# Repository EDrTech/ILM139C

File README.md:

&nbsp;
###### <sub>Quick access</sub>
---------------------------------------------------------------------------------

<p align="center">

</p>

---------------------------------------------------------------------------------
&nbsp;
&nbsp;
&nbsp;
---------------------------------------------------------------------------------
> [!WARNING]
> <p>
> This project is currently under active development. It is experimental, and may not function as intended. The source files might not exactly match tested hardware if you can see this message. Use at your own risk.
><br clear="right"/>
></p>

---------------------------------------------------------------------------------
# Illumicro ILM139C 13x9 RGB LED matrix

ILM139C Is an RGB LED module with a matrix of 13x9 RGB LEDs.
It is based on the IS31FL3741A LED matrix driver, which provides an i2c interface for full control of
individual LEDs which is accessible with a standard QWIIC connector. 
QWIIC Connector allows for up to 4 modules to be connected together on a single i2c bus.
Small form factor of 26mm*18mm and 2mm pitch of LEDs allows for creating small 
high density and high brightness displays.

https://github.com/user-attachments/assets/0ada246c-68c4-4b34-9f10-4a2aee3bf7c3

&nbsp;
&nbsp;
&nbsp;
&nbsp;
&nbsp;
&nbsp;
&nbsp;
&nbsp;
&nbsp;
&nbsp;

# Features
&nbsp;
&nbsp;
&nbsp;
&nbsp;
&nbsp;
<p>

- Very small footprint of 26mm*18mm
- 13x9 RBG LED matrix
- 1mm*1mm LEDs, with 2mm pitch
- IS31FL3741A Driver
- 2.7V~5.5V Operating voltage
- QWIIC Connector
- Selectable i2c address
- Removable driver/matrix boards
- Separate power supply connector
  
</p>
&nbsp;
&nbsp;
&nbsp;

# ILM139C Module pinout

---------------------------------------------------------------------------------

# Installation and set up

Connect QWIIC cable to one of the available connectors on the bottom of the module. If you want to power the module over QWIIC, the jumper resistor should be soldered on the bottom of the module. If the jumper is present, DO NOT connect external power supply as it will short to 3.3V of the QWIIC!
The module can be programmed over i2c, a library is currently under development to allow straightforward integration with and i2c capable device.

&nbsp;
&nbsp;
&nbsp;

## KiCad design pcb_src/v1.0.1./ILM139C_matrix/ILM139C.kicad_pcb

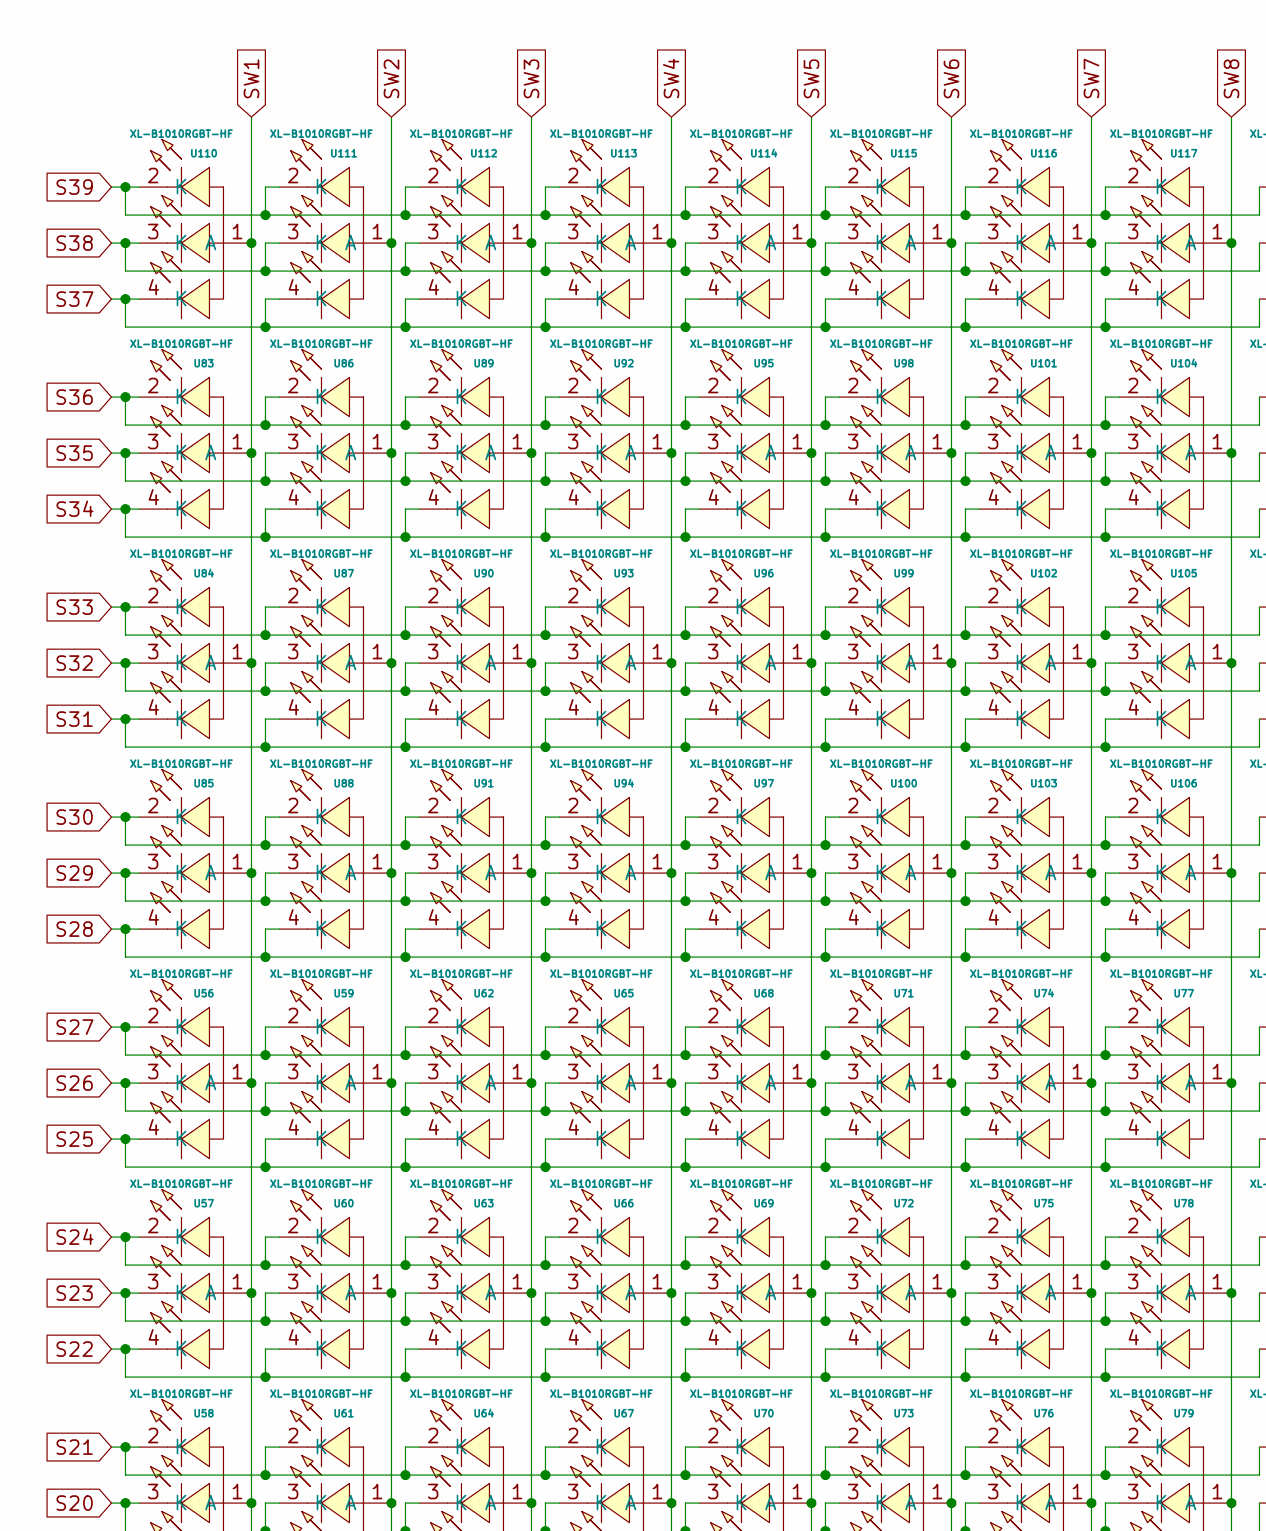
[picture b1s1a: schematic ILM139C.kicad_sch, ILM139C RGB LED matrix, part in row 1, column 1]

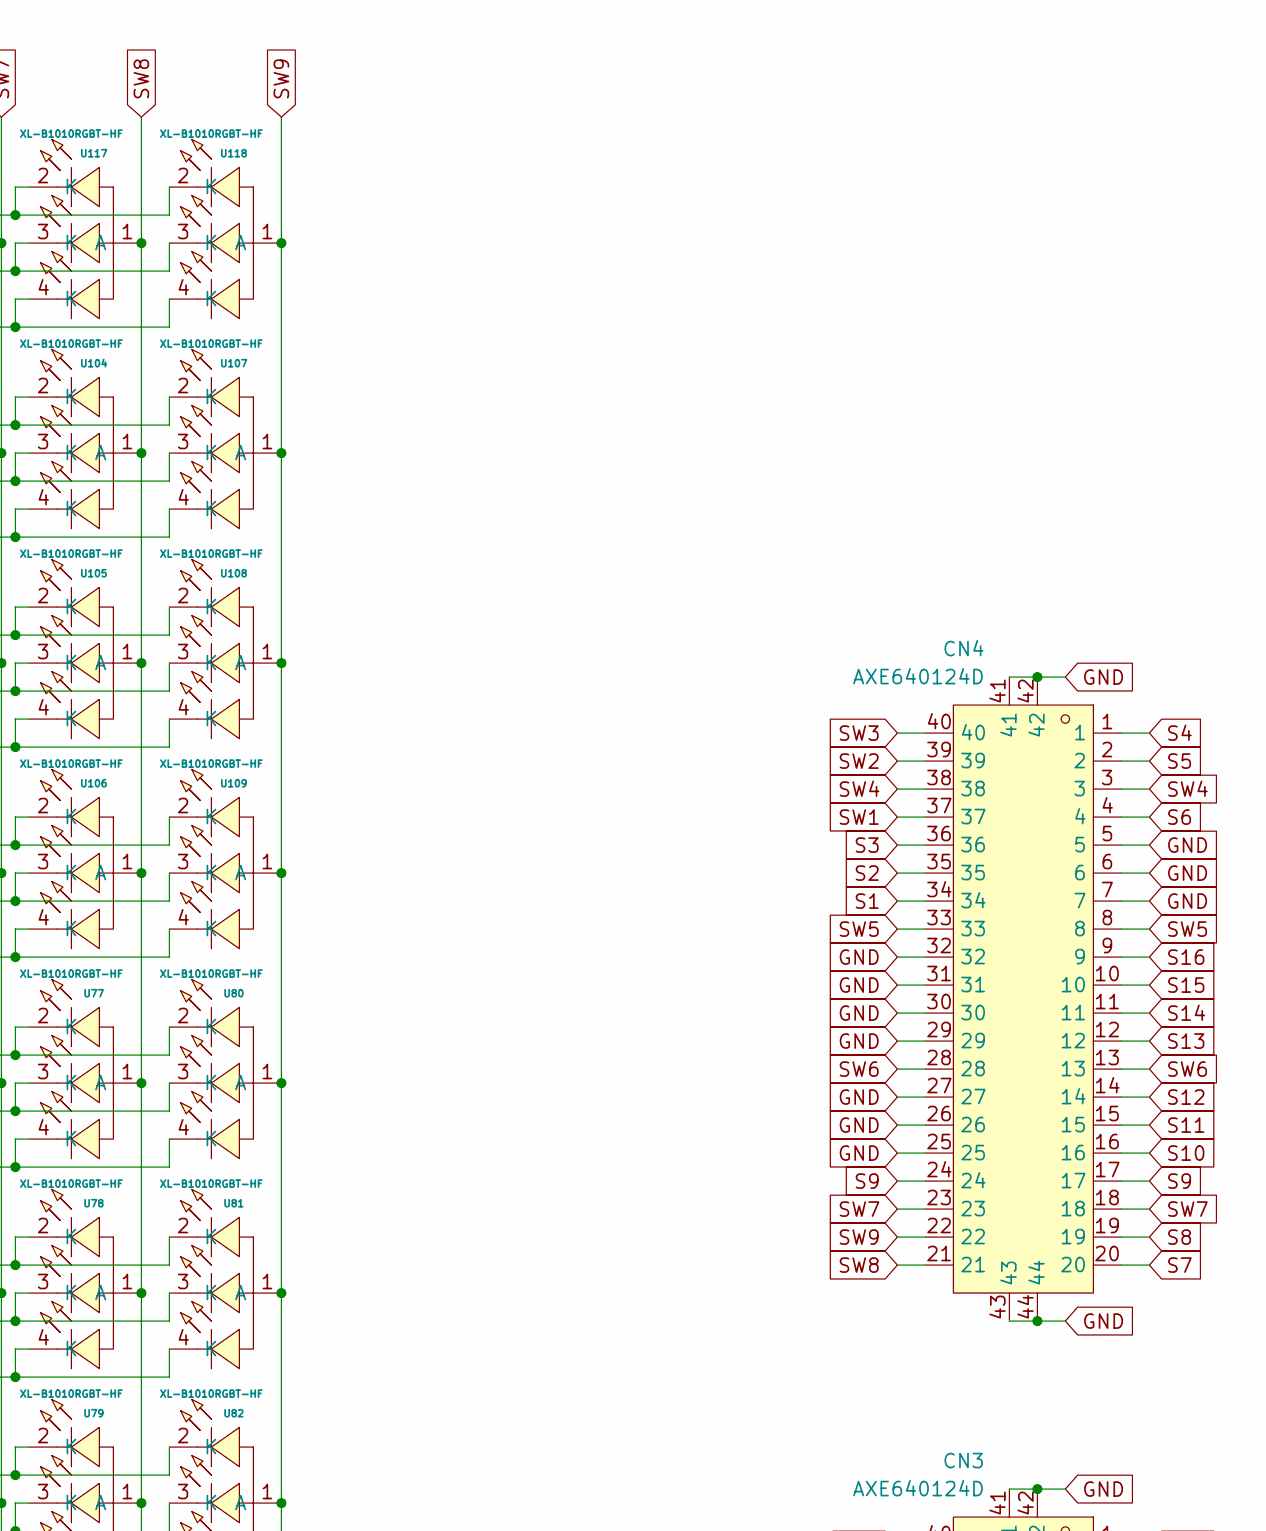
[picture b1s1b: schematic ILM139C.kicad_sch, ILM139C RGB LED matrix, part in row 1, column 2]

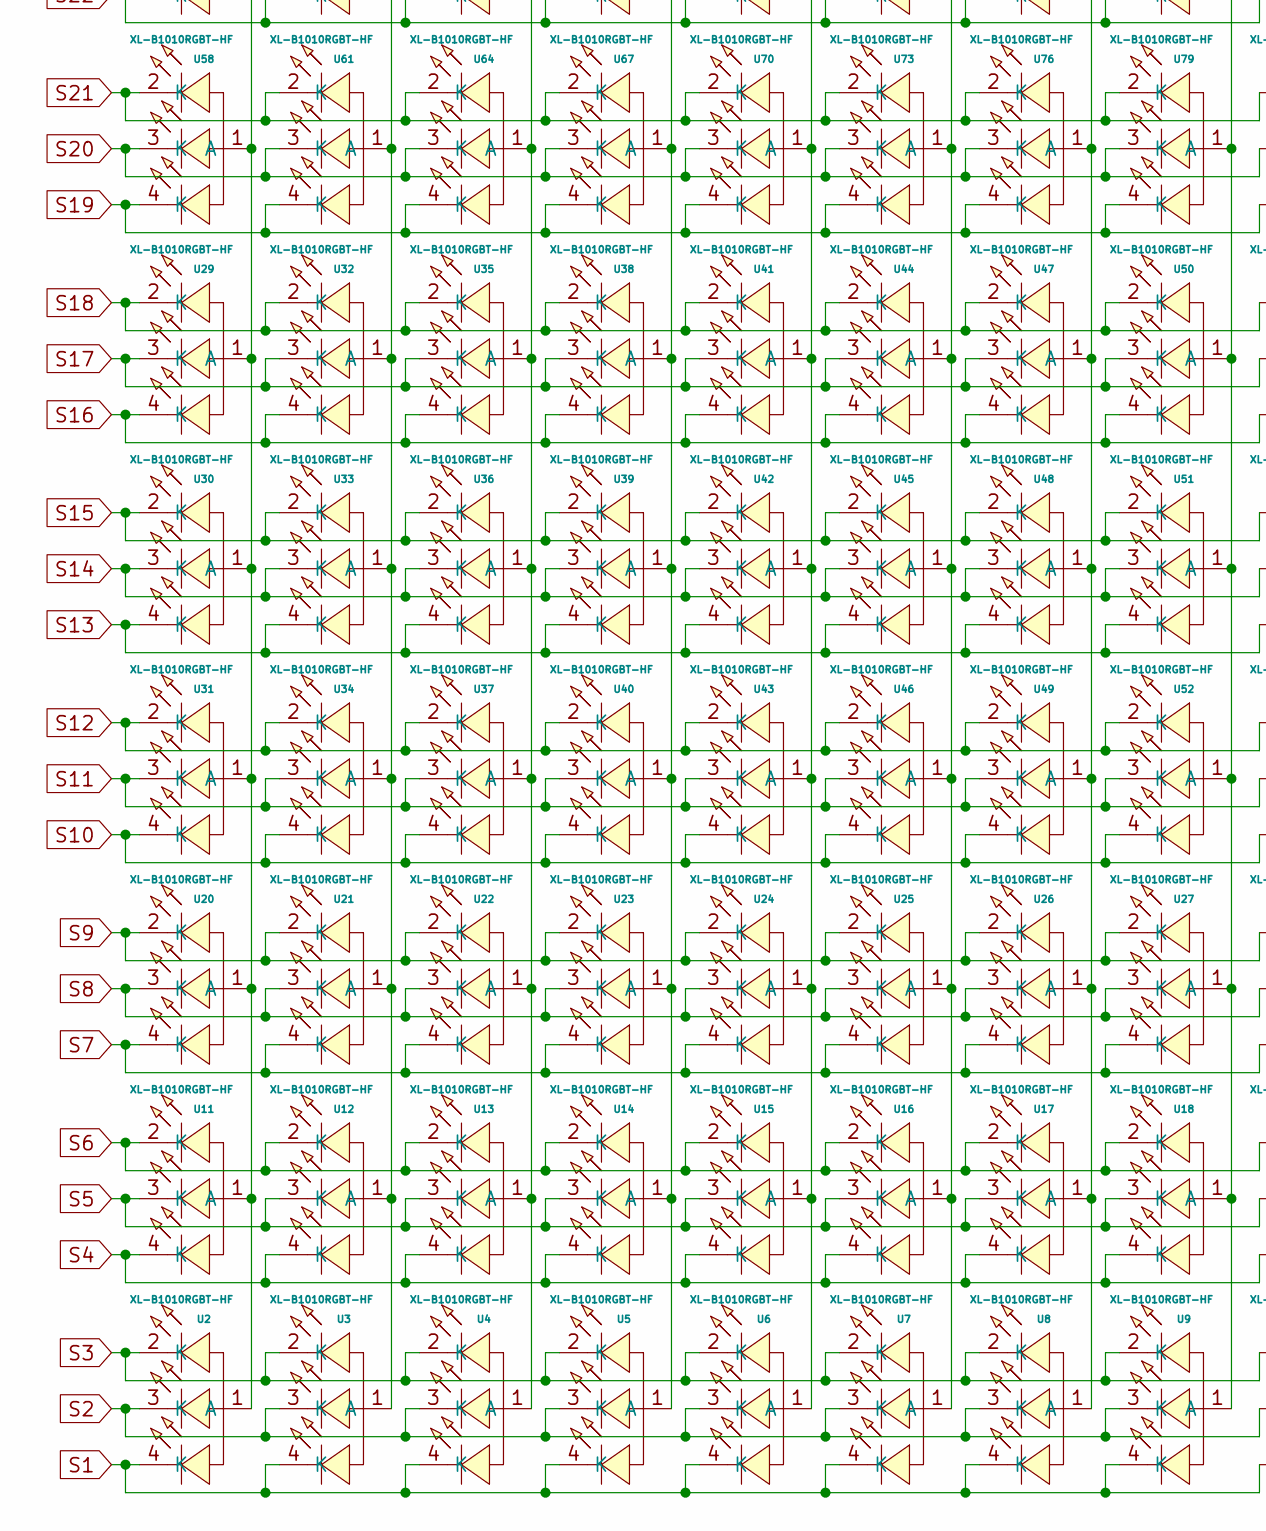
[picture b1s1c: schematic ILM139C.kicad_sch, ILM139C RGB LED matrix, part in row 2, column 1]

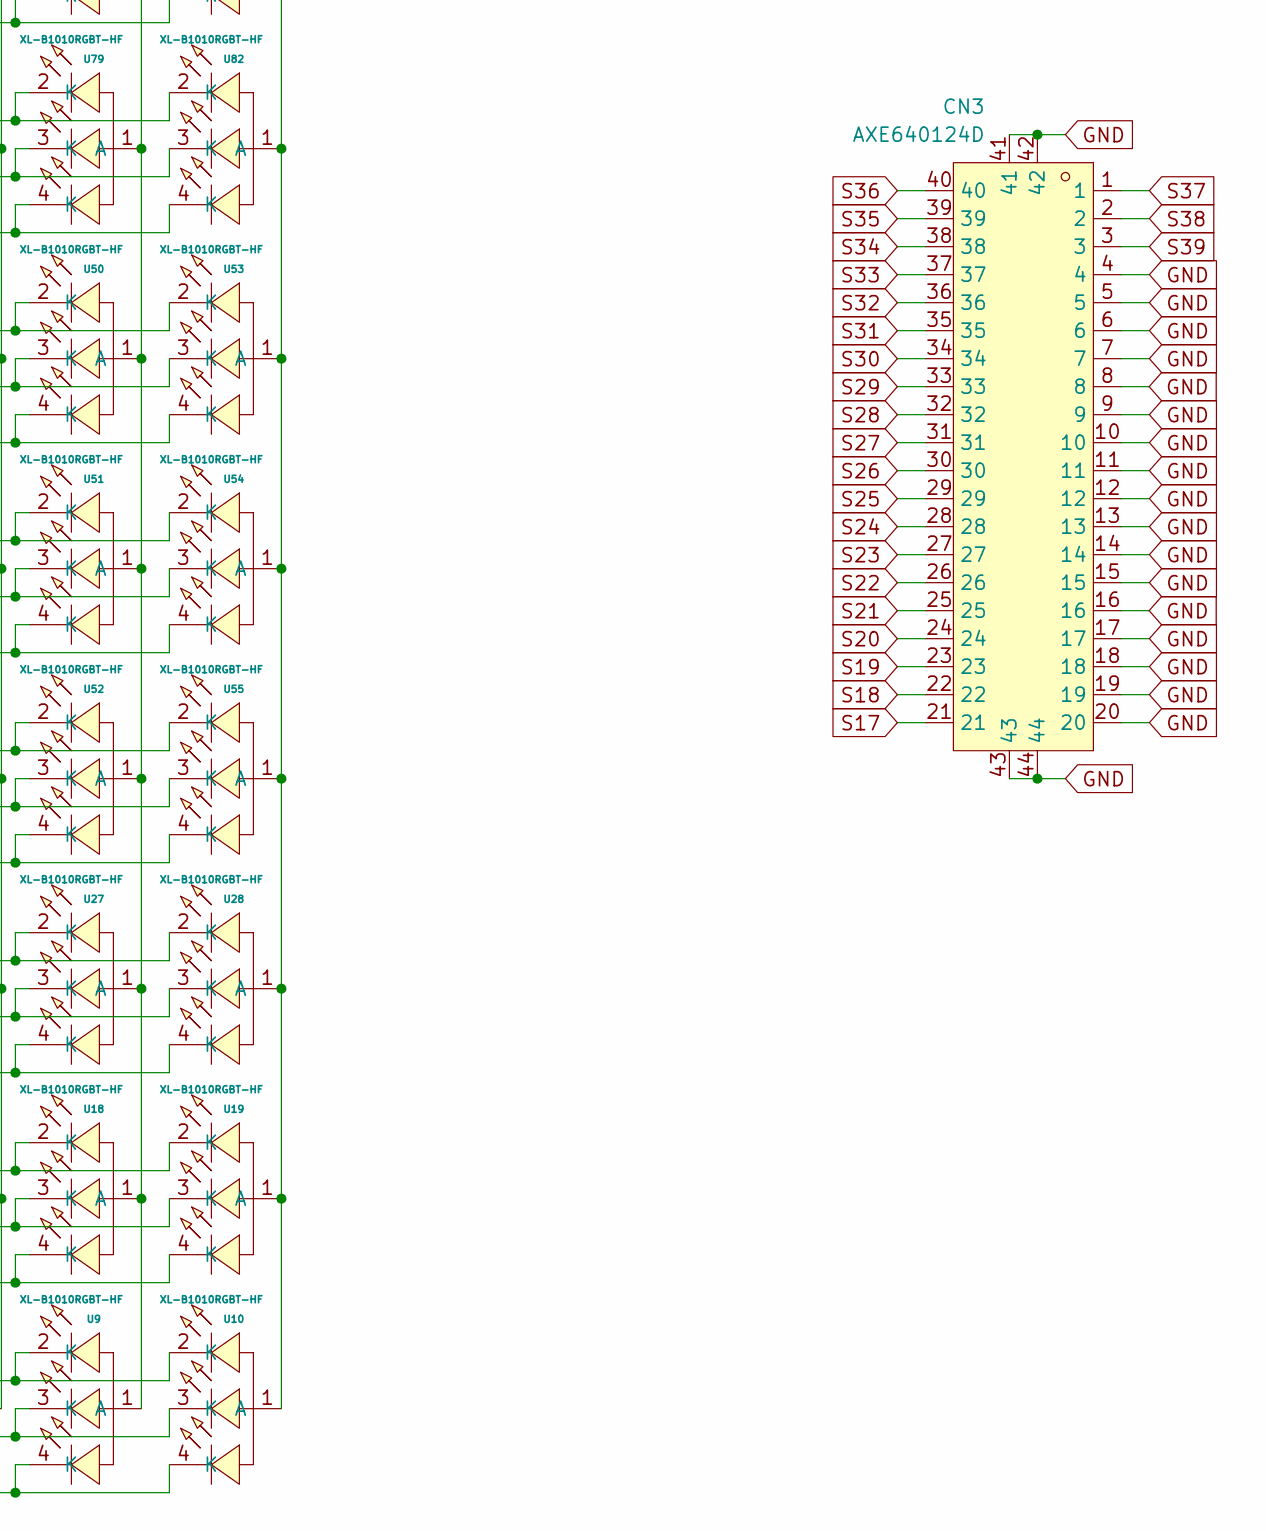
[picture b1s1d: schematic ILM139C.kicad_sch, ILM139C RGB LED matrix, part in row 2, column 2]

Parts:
CN3, CN4: AXE640124D; CONN-SMD_40P-P0.40_OK-14GM040-04; LCSC Part C5128265
U2, U3, U4, U5, U6, U7, U8, U9, U10, U11, U12, U13, U14, U15, U16, U17, U18, U19, U20, U21, U22, U23, U24, U25, U26, U27, U28, U29, U30, U31, U32, U33, U34, U35, U36, U37, U38, U39, U40, U41, U42, U43, U44, U45, U46, U47, U48, U49, U50, U51, U52, U53, U54, U55, U56, U57, U58, U59, U60, U61, U62, U63, U64, U65, U66, U67, U68, U69, U70, U71, U72, U73, U74, U75, U76, U77, U78, U79, U80, U81, U82, U83, U84, U85, U86, U87, U88, U89, U90, U91, U92, U93, U94, U95, U96, U97, U98, U99, U100, U101, U102, U103, U104, U105, U106, U107, U108, U109, U110, U111, U112, U113, U114, U115, U116, U117, U118: XL-B1010RGBT-HF; LED-SMD_4P-L1.0-W1.0-TR_1; LCSC Part C22464515

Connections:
GND: CN3.4, CN3.5, CN3.6, CN3.7, CN3.8, CN3.9, CN3.10, CN3.11, CN3.12, CN3.13, CN3.14, CN3.15, CN3.16, CN3.17, CN3.18, CN3.19, CN3.20, CN3.41, CN3.42, CN3.43, CN3.44, CN4.5, CN4.6, CN4.7, CN4.25, CN4.26, CN4.27, CN4.29, CN4.30, CN4.31, CN4.32, CN4.41, CN4.42, CN4.43, CN4.44
S1: CN4.34, U2.4 (K), U3.4 (K), U4.4 (K), U5.4 (K), U6.4 (K), U7.4 (K), U8.4 (K), U9.4 (K), U10.4 (K)
S2: CN4.35, U2.3 (K), U3.3 (K), U4.3 (K), U5.3 (K), U6.3 (K), U7.3 (K), U8.3 (K), U9.3 (K), U10.3 (K)
S3: CN4.36, U2.2 (K), U3.2 (K), U4.2 (K), U5.2 (K), U6.2 (K), U7.2 (K), U8.2 (K), U9.2 (K), U10.2 (K)
S4: CN4.1, U11.4 (K), U12.4 (K), U13.4 (K), U14.4 (K), U15.4 (K), U16.4 (K), U17.4 (K), U18.4 (K), U19.4 (K)
S5: CN4.2, U11.3 (K), U12.3 (K), U13.3 (K), U14.3 (K), U15.3 (K), U16.3 (K), U17.3 (K), U18.3 (K), U19.3 (K)
S6: CN4.4, U11.2 (K), U12.2 (K), U13.2 (K), U14.2 (K), U15.2 (K), U16.2 (K), U17.2 (K), U18.2 (K), U19.2 (K)
S7: CN4.20, U20.4 (K), U21.4 (K), U22.4 (K), U23.4 (K), U24.4 (K), U25.4 (K), U26.4 (K), U27.4 (K), U28.4 (K)
S8: CN4.19, U20.3 (K), U21.3 (K), U22.3 (K), U23.3 (K), U24.3 (K), U25.3 (K), U26.3 (K), U27.3 (K), U28.3 (K)
S9: CN4.17, CN4.24, U20.2 (K), U21.2 (K), U22.2 (K), U23.2 (K), U24.2 (K), U25.2 (K), U26.2 (K), U27.2 (K), U28.2 (K)
S10: CN4.16, U31.4 (K), U34.4 (K), U37.4 (K), U40.4 (K), U43.4 (K), U46.4 (K), U49.4 (K), U52.4 (K), U55.4 (K)
S11: CN4.15, U31.3 (K), U34.3 (K), U37.3 (K), U40.3 (K), U43.3 (K), U46.3 (K), U49.3 (K), U52.3 (K), U55.3 (K)
S12: CN4.14, U31.2 (K), U34.2 (K), U37.2 (K), U40.2 (K), U43.2 (K), U46.2 (K), U49.2 (K), U52.2 (K), U55.2 (K)
S13: CN4.12, U30.4 (K), U33.4 (K), U36.4 (K), U39.4 (K), U42.4 (K), U45.4 (K), U48.4 (K), U51.4 (K), U54.4 (K)
S14: CN4.11, U30.3 (K), U33.3 (K), U36.3 (K), U39.3 (K), U42.3 (K), U45.3 (K), U48.3 (K), U51.3 (K), U54.3 (K)
S15: CN4.10, U30.2 (K), U33.2 (K), U36.2 (K), U39.2 (K), U42.2 (K), U45.2 (K), U48.2 (K), U51.2 (K), U54.2 (K)
S16: CN4.9, U29.4 (K), U32.4 (K), U35.4 (K), U38.4 (K), U41.4 (K), U44.4 (K), U47.4 (K), U50.4 (K), U53.4 (K)
S17: CN3.21, U29.3 (K), U32.3 (K), U35.3 (K), U38.3 (K), U41.3 (K), U44.3 (K), U47.3 (K), U50.3 (K), U53.3 (K)
S18: CN3.22, U29.2 (K), U32.2 (K), U35.2 (K), U38.2 (K), U41.2 (K), U44.2 (K), U47.2 (K), U50.2 (K), U53.2 (K)
S19: CN3.23, U58.4 (K), U61.4 (K), U64.4 (K), U67.4 (K), U70.4 (K), U73.4 (K), U76.4 (K), U79.4 (K), U82.4 (K)
S20: CN3.24, U58.3 (K), U61.3 (K), U64.3 (K), U67.3 (K), U70.3 (K), U73.3 (K), U76.3 (K), U79.3 (K), U82.3 (K)
S21: CN3.25, U58.2 (K), U61.2 (K), U64.2 (K), U67.2 (K), U70.2 (K), U73.2 (K), U76.2 (K), U79.2 (K), U82.2 (K)
S22: CN3.26, U57.4 (K), U60.4 (K), U63.4 (K), U66.4 (K), U69.4 (K), U72.4 (K), U75.4 (K), U78.4 (K), U81.4 (K)
S23: CN3.27, U57.3 (K), U60.3 (K), U63.3 (K), U66.3 (K), U69.3 (K), U72.3 (K), U75.3 (K), U78.3 (K), U81.3 (K)
S24: CN3.28, U57.2 (K), U60.2 (K), U63.2 (K), U66.2 (K), U69.2 (K), U72.2 (K), U75.2 (K), U78.2 (K), U81.2 (K)
S25: CN3.29, U56.4 (K), U59.4 (K), U62.4 (K), U65.4 (K), U68.4 (K), U71.4 (K), U74.4 (K), U77.4 (K), U80.4 (K)
S26: CN3.30, U56.3 (K), U59.3 (K), U62.3 (K), U65.3 (K), U68.3 (K), U71.3 (K), U74.3 (K), U77.3 (K), U80.3 (K)
S27: CN3.31, U56.2 (K), U59.2 (K), U62.2 (K), U65.2 (K), U68.2 (K), U71.2 (K), U74.2 (K), U77.2 (K), U80.2 (K)
S28: CN3.32, U85.4 (K), U88.4 (K), U91.4 (K), U94.4 (K), U97.4 (K), U100.4 (K), U103.4 (K), U106.4 (K), U109.4 (K)
S29: CN3.33, U85.3 (K), U88.3 (K), U91.3 (K), U94.3 (K), U97.3 (K), U100.3 (K), U103.3 (K), U106.3 (K), U109.3 (K)
S30: CN3.34, U85.2 (K), U88.2 (K), U91.2 (K), U94.2 (K), U97.2 (K), U100.2 (K), U103.2 (K), U106.2 (K), U109.2 (K)
S31: CN3.35, U84.4 (K), U87.4 (K), U90.4 (K), U93.4 (K), U96.4 (K), U99.4 (K), U102.4 (K), U105.4 (K), U108.4 (K)
S32: CN3.36, U84.3 (K), U87.3 (K), U90.3 (K), U93.3 (K), U96.3 (K), U99.3 (K), U102.3 (K), U105.3 (K), U108.3 (K)
S33: CN3.37, U84.2 (K), U87.2 (K), U90.2 (K), U93.2 (K), U96.2 (K), U99.2 (K), U102.2 (K), U105.2 (K), U108.2 (K)
S34: CN3.38, U83.4 (K), U86.4 (K), U89.4 (K), U92.4 (K), U95.4 (K), U98.4 (K), U101.4 (K), U104.4 (K), U107.4 (K)
S35: CN3.39, U83.3 (K), U86.3 (K), U89.3 (K), U92.3 (K), U95.3 (K), U98.3 (K), U101.3 (K), U104.3 (K), U107.3 (K)
S36: CN3.40, U83.2 (K), U86.2 (K), U89.2 (K), U92.2 (K), U95.2 (K), U98.2 (K), U101.2 (K), U104.2 (K), U107.2 (K)
S37: CN3.1, U110.4 (K), U111.4 (K), U112.4 (K), U113.4 (K), U114.4 (K), U115.4 (K), U116.4 (K), U117.4 (K), U118.4 (K)
S38: CN3.2, U110.3 (K), U111.3 (K), U112.3 (K), U113.3 (K), U114.3 (K), U115.3 (K), U116.3 (K), U117.3 (K), U118.3 (K)
S39: CN3.3, U110.2 (K), U111.2 (K), U112.2 (K), U113.2 (K), U114.2 (K), U115.2 (K), U116.2 (K), U117.2 (K), U118.2 (K)
SW1: CN4.37, U2.1 (A), U11.1 (A), U20.1 (A), U29.1 (A), U30.1 (A), U31.1 (A), U56.1 (A), U57.1 (A), U58.1 (A), U83.1 (A), U84.1 (A), U85.1 (A), U110.1 (A)
SW2: CN4.39, U3.1 (A), U12.1 (A), U21.1 (A), U32.1 (A), U33.1 (A), U34.1 (A), U59.1 (A), U60.1 (A), U61.1 (A), U86.1 (A), U87.1 (A), U88.1 (A), U111.1 (A)
SW3: CN4.40, U4.1 (A), U13.1 (A), U22.1 (A), U35.1 (A), U36.1 (A), U37.1 (A), U62.1 (A), U63.1 (A), U64.1 (A), U89.1 (A), U90.1 (A), U91.1 (A), U112.1 (A)
SW4: CN4.3, CN4.38, U5.1 (A), U14.1 (A), U23.1 (A), U38.1 (A), U39.1 (A), U40.1 (A), U65.1 (A), U66.1 (A), U67.1 (A), U92.1 (A), U93.1 (A), U94.1 (A), U113.1 (A)
SW5: CN4.8, CN4.33, U6.1 (A), U15.1 (A), U24.1 (A), U41.1 (A), U42.1 (A), U43.1 (A), U68.1 (A), U69.1 (A), U70.1 (A), U95.1 (A), U96.1 (A), U97.1 (A), U114.1 (A)
SW6: CN4.13, CN4.28, U7.1 (A), U16.1 (A), U25.1 (A), U44.1 (A), U45.1 (A), U46.1 (A), U71.1 (A), U72.1 (A), U73.1 (A), U98.1 (A), U99.1 (A), U100.1 (A), U115.1 (A)
SW7: CN4.18, CN4.23, U8.1 (A), U17.1 (A), U26.1 (A), U47.1 (A), U48.1 (A), U49.1 (A), U74.1 (A), U75.1 (A), U76.1 (A), U101.1 (A), U102.1 (A), U103.1 (A), U116.1 (A)
SW8: CN4.21, U9.1 (A), U18.1 (A), U27.1 (A), U50.1 (A), U51.1 (A), U52.1 (A), U77.1 (A), U78.1 (A), U79.1 (A), U104.1 (A), U105.1 (A), U106.1 (A), U117.1 (A)
SW9: CN4.22, U10.1 (A), U19.1 (A), U28.1 (A), U53.1 (A), U54.1 (A), U55.1 (A), U80.1 (A), U81.1 (A), U82.1 (A), U107.1 (A), U108.1 (A), U109.1 (A), U118.1 (A)

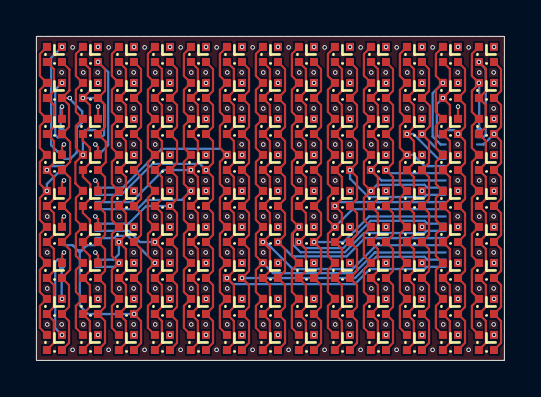
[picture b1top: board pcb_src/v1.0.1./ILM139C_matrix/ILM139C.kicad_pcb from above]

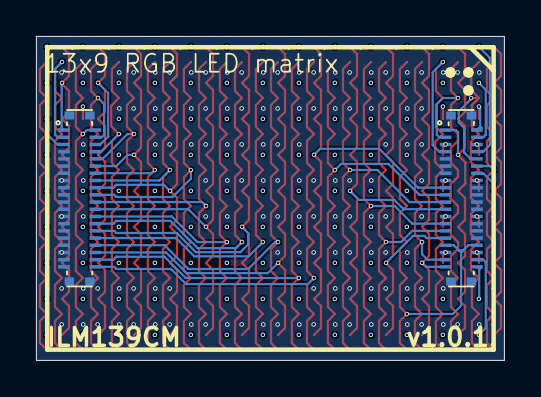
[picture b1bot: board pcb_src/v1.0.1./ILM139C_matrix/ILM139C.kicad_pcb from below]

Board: 4 copper layers, 26.0 x 18.0 mm, 119 parts (2 on the bottom side), 49 nets.

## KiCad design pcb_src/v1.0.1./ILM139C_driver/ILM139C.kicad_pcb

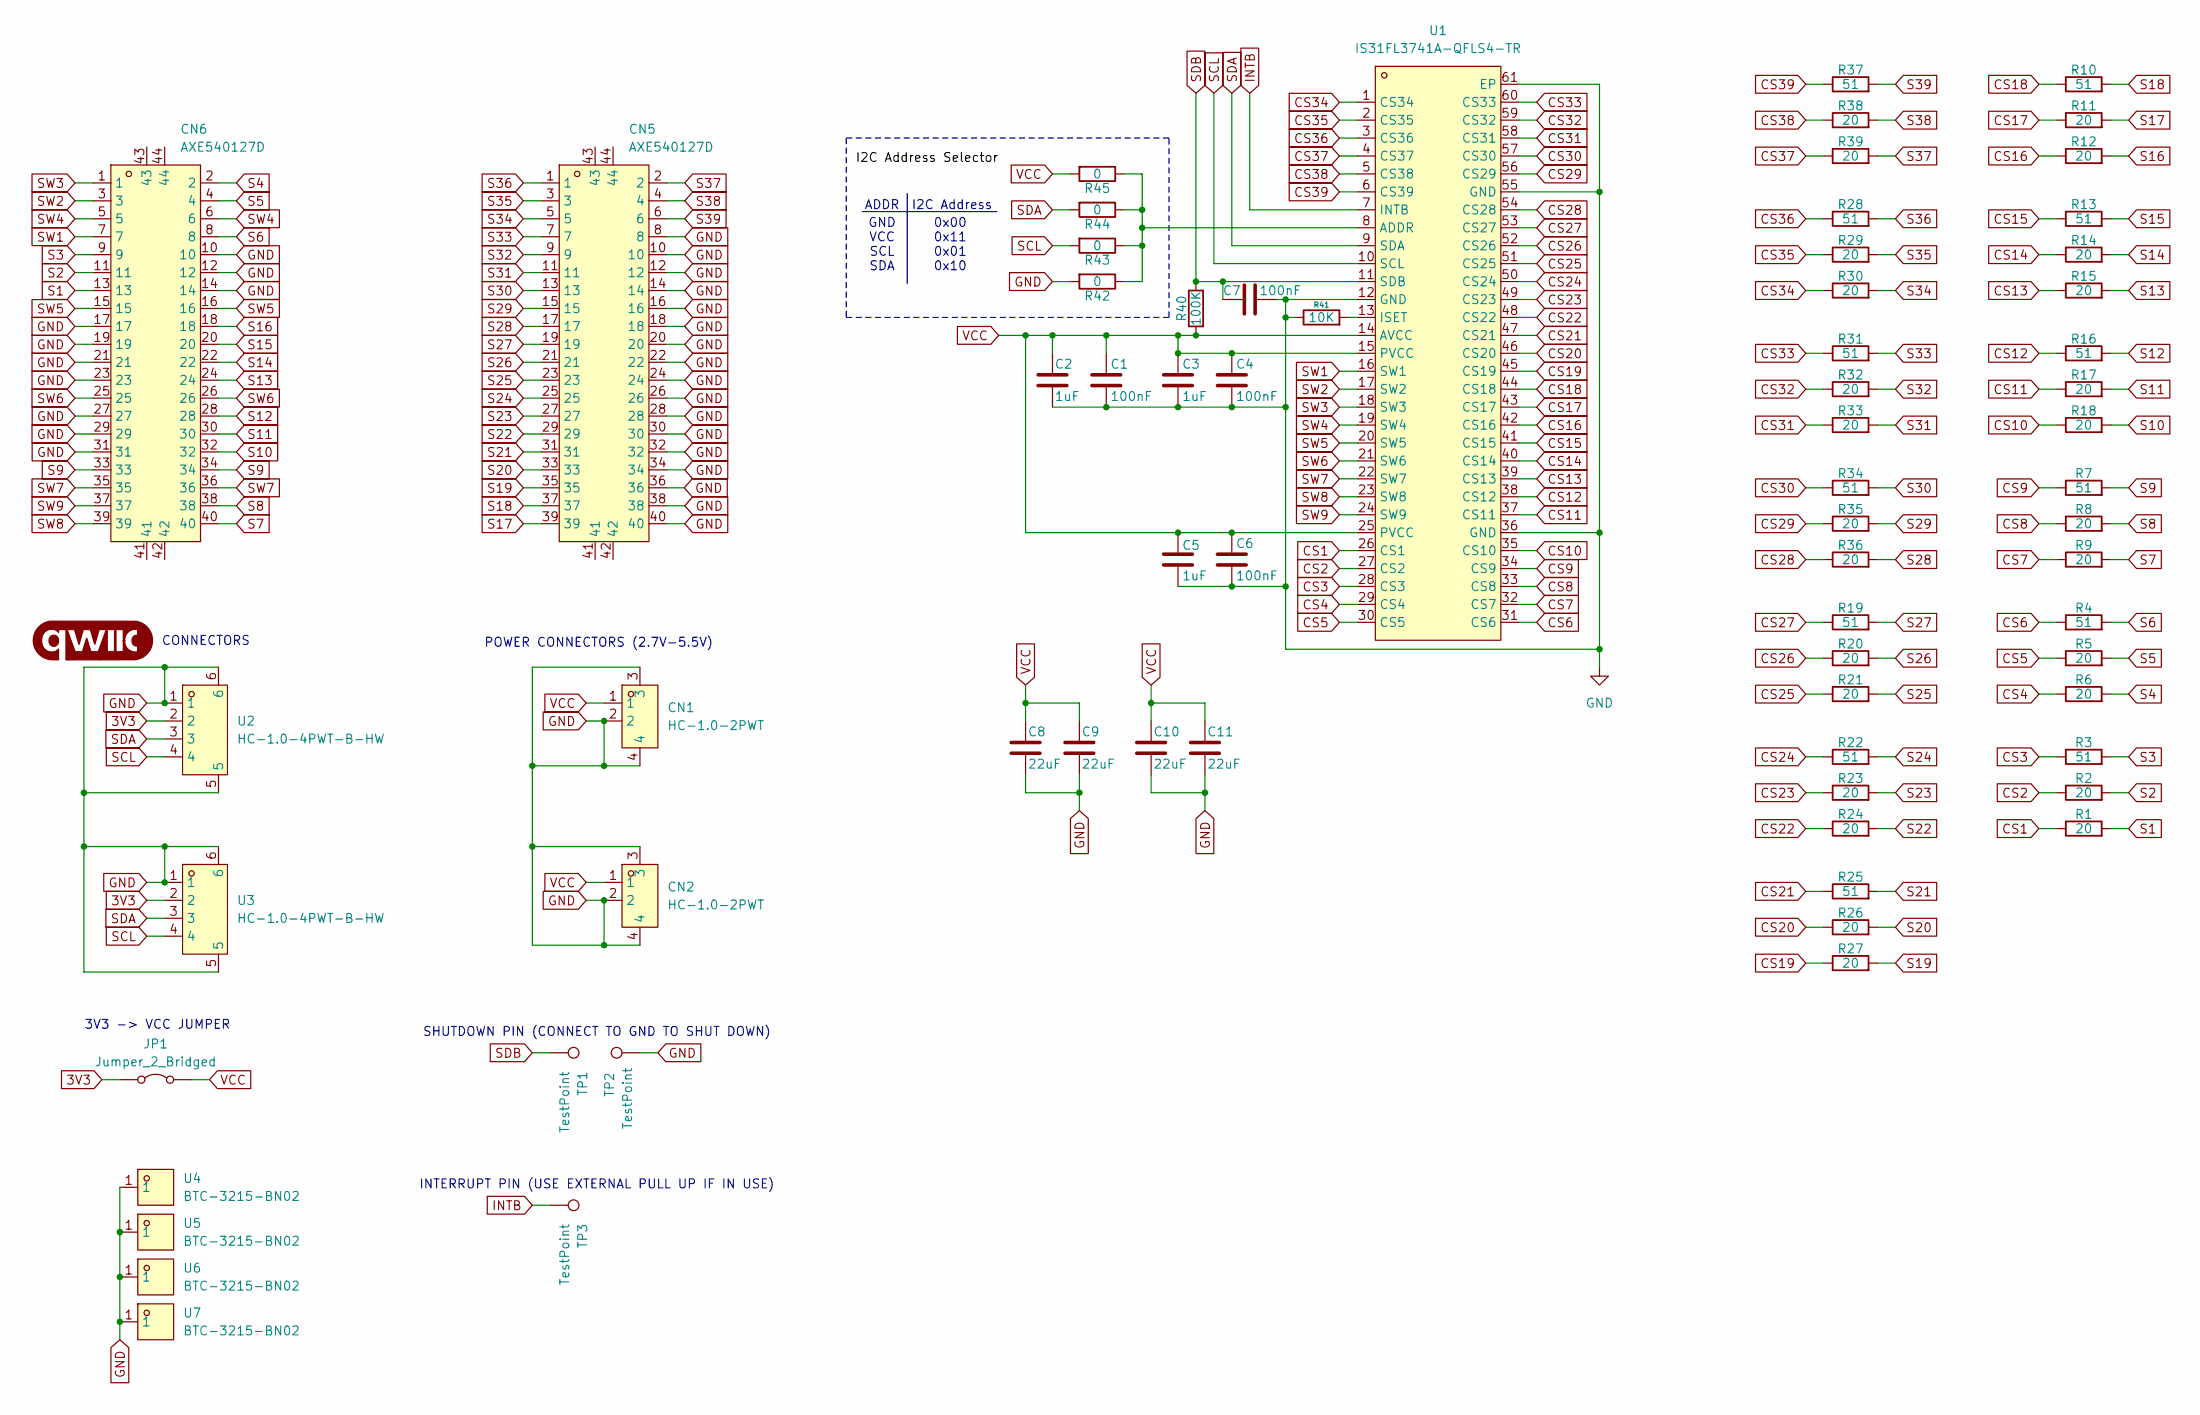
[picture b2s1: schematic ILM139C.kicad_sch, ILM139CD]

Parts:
C1, C4, C6, C7: 100nF; C_0402_1005Metric
C2, C3, C5: 1uF; C_0402_1005Metric
C8, C9, C10: 22uF; C_0805_2012Metric
C11: 22uF; C_0603_1608Metric
CN1, CN2: HC-1.0-2PWT; CONN-SMD_HC-1.0-2PWT; LCSC Part C2845361
CN5, CN6: AXE540127D; CONN-SMD_40P-P0.40_AXE540127D; LCSC Part C2982234
G1: qwiic_Logo; qwiic_3mm
JP1: Jumper_2_Bridged; SolderJumper-2_P1.3mm_Bridged2Bar_RoundedPad1.0x1.5mm
R1, R2, R5, R6, R8, R9, R11, R12, R14, R15, R17, R18, R20, R21, R23, R24, R26, R27, R29, R30, R32, R33, R35, R36, R38, R39: 20; R_0603_1608Metric
R3, R4, R7, R10, R13, R16, R19, R22, R25, R28, R31, R34, R37: 51; R_0603_1608Metric
R40: 100K; R_0402_1005Metric
R41: 10K; R_0402_1005Metric
R42, R43, R44, R45: 0; R_0603_1608Metric
TP1, TP2, TP3: TestPoint; TestPoint_Pad_D1.0mm
U1: IS31FL3741A-QFLS4-TR; QFN-60_L7.0-W7.0-P0.40-TL-EP5.3; LCSC Part C2940604
U2, U3: HC-1.0-4PWT-B-HW; CONN-SMD_4P-P1.00_HCTL_HC-1.0-4PWT; LCSC Part C19270571
U4, U5, U6, U7: BTC-3215-BN02; SMD-1_L3.0-W2.0-H1.5; LCSC Part C34373670

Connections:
3V3: JP1.1 (A), U2.2, U3.2
CS1: R1.1, U1.26 (CS1)
CS2: R2.1, U1.27 (CS2)
CS3: R3.1, U1.28 (CS3)
CS4: R6.1, U1.29 (CS4)
CS5: R5.1, U1.30 (CS5)
CS6: R4.1, U1.31 (CS6)
CS7: R9.1, U1.32 (CS7)
CS8: R8.1, U1.33 (CS8)
CS9: R7.1, U1.34 (CS9)
CS10: R18.1, U1.35 (CS10)
CS11: R17.1, U1.37 (CS11)
CS12: R16.1, U1.38 (CS12)
CS13: R15.1, U1.39 (CS13)
CS14: R14.1, U1.40 (CS14)
CS15: R13.1, U1.41 (CS15)
CS16: R12.1, U1.42 (CS16)
CS17: R11.1, U1.43 (CS17)
CS18: R10.1, U1.44 (CS18)
CS19: R27.1, U1.45 (CS19)
CS20: R26.1, U1.46 (CS20)
CS21: R25.1, U1.47 (CS21)
CS22: R24.1, U1.48 (CS22)
CS23: R23.1, U1.49 (CS23)
CS24: R22.1, U1.50 (CS24)
CS25: R21.1, U1.51 (CS25)
CS26: R20.1, U1.52 (CS26)
CS27: R19.1, U1.53 (CS27)
CS28: R36.1, U1.54 (CS28)
CS29: R35.1, U1.56 (CS29)
CS30: R34.1, U1.57 (CS30)
CS31: R33.1, U1.58 (CS31)
CS32: R32.1, U1.59 (CS32)
CS33: R31.1, U1.60 (CS33)
CS34: R30.1, U1.1 (CS34)
CS35: R29.1, U1.2 (CS35)
CS36: R28.1, U1.3 (CS36)
CS37: R39.1, U1.4 (CS37)
CS38: R38.1, U1.5 (CS38)
CS39: R37.1, U1.6 (CS39)
GND: C1.2, C2.2, C3.2, C4.2, C5.2, C6.2, C7.2, C8.2, C9.2, C10.2, C11.2, CN1.2, CN1.3, CN1.4, CN2.2, CN2.3, CN2.4, CN5.8, CN5.10, CN5.12, CN5.14, CN5.16, CN5.18, CN5.20, CN5.22, CN5.24, CN5.26, CN5.28, CN5.30, CN5.32, CN5.34, CN5.36, CN5.38, CN5.40, CN6.10, CN6.12, CN6.14, CN6.17, CN6.19, CN6.21, CN6.23, CN6.27, CN6.29, CN6.31, R41.1, R42.2, TP2.1, U1.12 (GND), U1.36 (GND), U1.55 (GND), U1.61 (EP), U2.1, U2.5, U2.6, U3.1, U3.5, U3.6, U4.1, U5.1, U6.1, U7.1
INTB: TP3.1, U1.7 (INTB)
unnamed: R42.1, R43.1, R44.1, R45.1, U1.8 (ADDR)
unnamed: R41.2, U1.13 (ISET)
S1: CN6.13, R1.2
S2: CN6.11, R2.2
S3: CN6.9, R3.2
S4: CN6.2, R6.2
S5: CN6.4, R5.2
S6: CN6.8, R4.2
S7: CN6.40, R9.2
S8: CN6.38, R8.2
S9: CN6.33, CN6.34, R7.2
S10: CN6.32, R18.2
S11: CN6.30, R17.2
S12: CN6.28, R16.2
S13: CN6.24, R15.2
S14: CN6.22, R14.2
S15: CN6.20, R13.2
S16: CN6.18, R12.2
S17: CN5.39, R11.2
S18: CN5.37, R10.2
S19: CN5.35, R27.2
S20: CN5.33, R26.2
S21: CN5.31, R25.2
S22: CN5.29, R24.2
S23: CN5.27, R23.2
S24: CN5.25, R22.2
S25: CN5.23, R21.2
S26: CN5.21, R20.2
S27: CN5.19, R19.2
S28: CN5.17, R36.2
S29: CN5.15, R35.2
S30: CN5.13, R34.2
S31: CN5.11, R33.2
S32: CN5.9, R32.2
S33: CN5.7, R31.2
S34: CN5.5, R30.2
S35: CN5.3, R29.2
S36: CN5.1, R28.2
S37: CN5.2, R39.2
S38: CN5.4, R38.2
S39: CN5.6, R37.2
SCL: R43.2, U1.10 (SCL), U2.4, U3.4
SDA: R44.2, U1.9 (SDA), U2.3, U3.3
SDB: C7.1, R40.2, TP1.1, U1.11 (SDB)
SW1: CN6.7, U1.16 (SW1)
SW2: CN6.3, U1.17 (SW2)
SW3: CN6.1, U1.18 (SW3)
SW4: CN6.5, CN6.6, U1.19 (SW4)
SW5: CN6.15, CN6.16, U1.20 (SW5)
SW6: CN6.25, CN6.26, U1.21 (SW6)
SW7: CN6.35, CN6.36, U1.22 (SW7)
SW8: CN6.39, U1.23 (SW8)
SW9: CN6.37, U1.24 (SW9)
VCC: C1.1, C2.1, C3.1, C4.1, C5.1, C6.1, C8.1, C9.1, C10.1, C11.1, CN1.1, CN2.1, JP1.2 (B), R40.1, R45.2, U1.14 (AVCC), U1.15 (PVCC), U1.25 (PVCC)

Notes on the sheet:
ADDR
CONNECTORS
POWER CONNECTORS (2.7V-5.5V)
3V3 -> VCC JUMPER
SHUTDOWN PIN (CONNECT TO GND TO SHUT DOWN)
INTERRUPT PIN (USE EXTERNAL PULL UP IF IN USE)
GND VCC SCL SDA
0x00 0x11 0x01 0x10
I2C Address

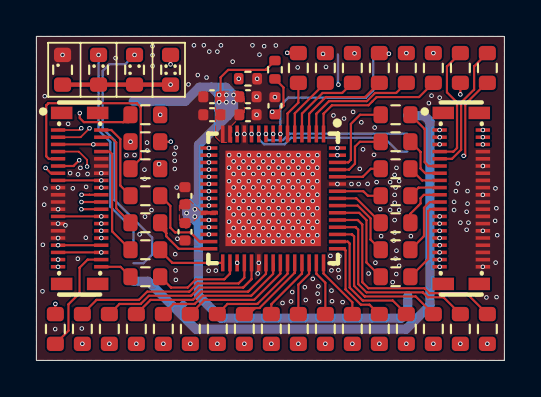
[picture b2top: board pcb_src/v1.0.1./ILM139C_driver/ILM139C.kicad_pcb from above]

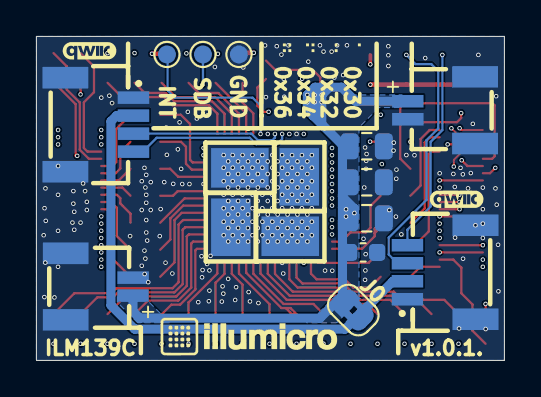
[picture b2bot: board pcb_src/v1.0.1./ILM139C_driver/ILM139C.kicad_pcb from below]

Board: 4 copper layers, 26.0 x 18.0 mm, 71 parts (16 on the bottom side), 96 nets.

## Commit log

2025-04-18 setup
2025-04-23 First board design
2025-04-24 Matrix design, visual
2025-04-25 Added 2x2 panel
2025-04-26 Added driver module
2025-04-26 QWIIC things added
2025-04-28 added docs
2025-05-06 Cleaned up, added images
2025-05-07 Added documentation
2025-05-07 Documentation edited
2025-05-07 Added badges
2025-05-07 Added pinout, fixed qwiic
2025-05-08 Pinout corrected
2025-05-10 Added production files
2025-05-13 Added datasheet related stuff
2025-05-19 Added license.
2025-06-27 Updated, added lib & demo code
2025-07-04 Updated to latest version
2025-07-05 Added graphics
2025-07-05 Added pinout
2025-07-05 Added blueprint
2025-07-05 Added demo video
2025-07-18 Cleaned repo
